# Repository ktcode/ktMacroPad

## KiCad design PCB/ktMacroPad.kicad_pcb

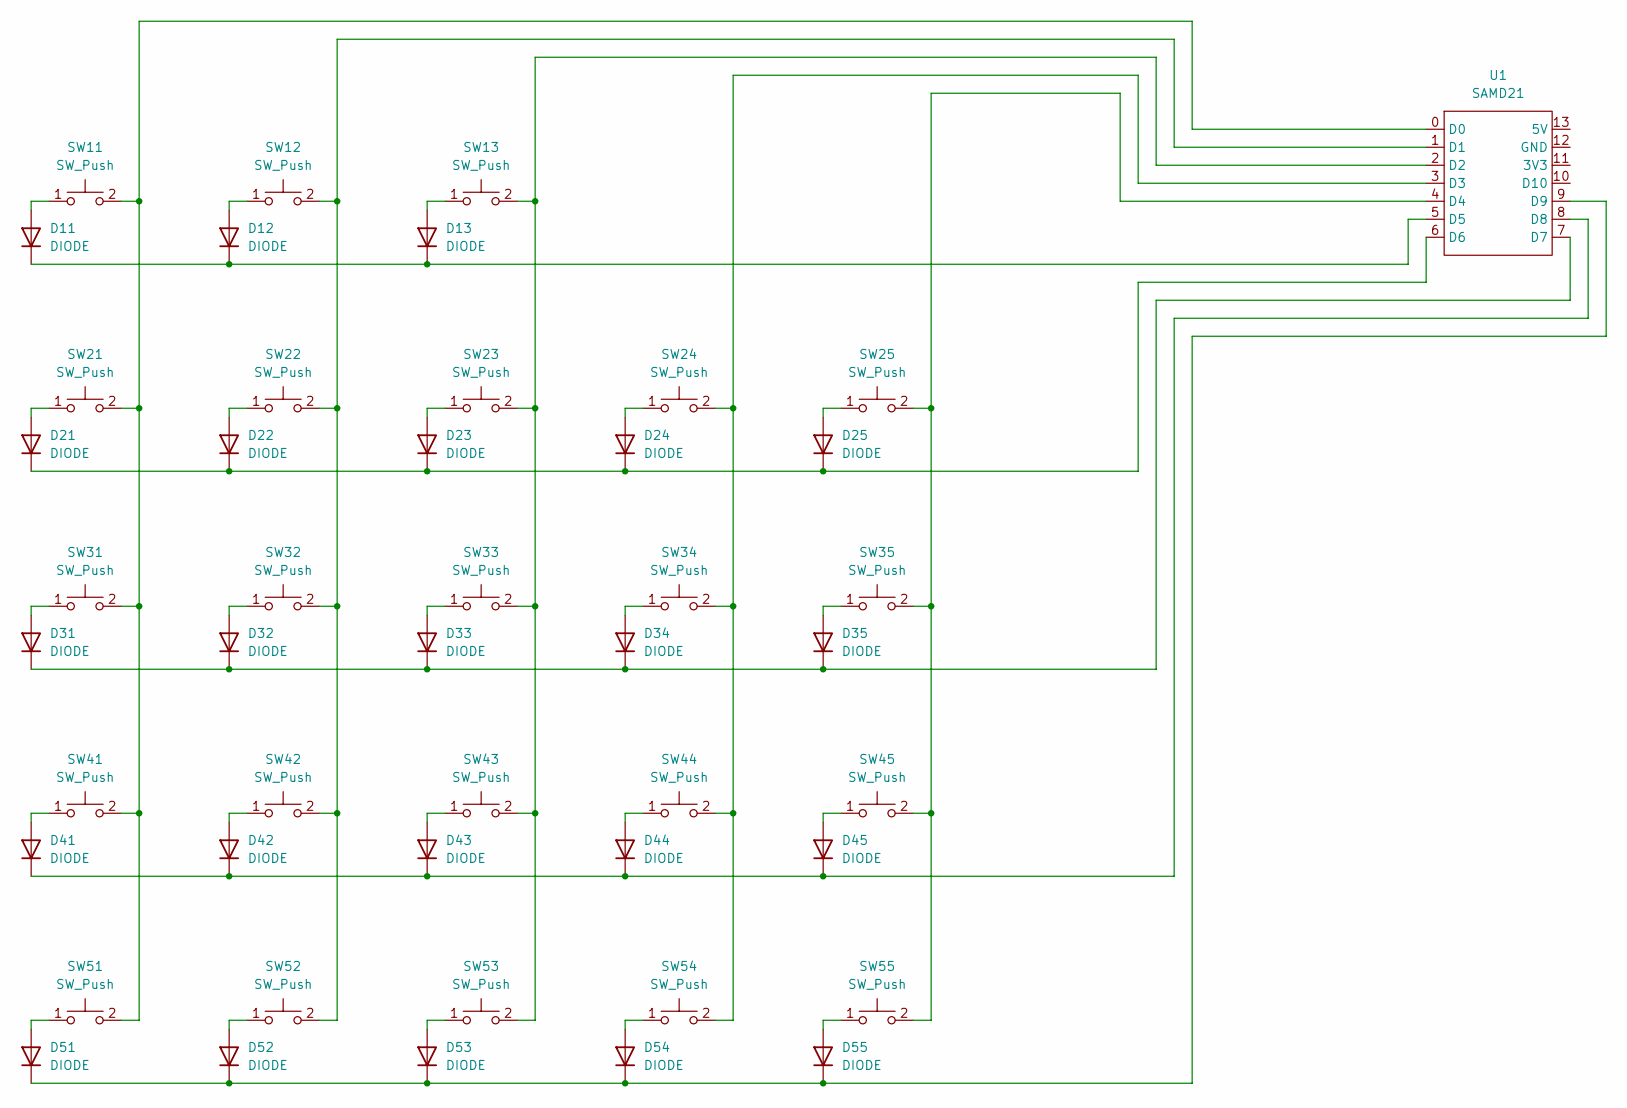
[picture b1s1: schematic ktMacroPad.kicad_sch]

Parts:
D11, D12, D13, D21, D22, D23, D24, D25, D31, D32, D33, D34, D35, D41, D42, D43, D44, D45, D51, D52, D53, D54, D55: DIODE; DI
SW11, SW12, SW13, SW21, SW22, SW23, SW24, SW25, SW31, SW32, SW33, SW34, SW35, SW41, SW42, SW43, SW44, SW45, SW51, SW52, SW53, SW54, SW55: SW_Push; MX_Choc_Socket
U1: SAMD21; Seeed xiao

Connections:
unnamed: D11.1 (A), SW11.1
unnamed: D11.2 (K), D12.2 (K), D13.2 (K), U1.5 (D5)
unnamed: D12.1 (A), SW12.1
unnamed: D13.1 (A), SW13.1
unnamed: D21.1 (A), SW21.1
unnamed: D21.2 (K), D22.2 (K), D23.2 (K), D24.2 (K), D25.2 (K), U1.6 (D6)
unnamed: D22.1 (A), SW22.1
unnamed: D23.1 (A), SW23.1
unnamed: D24.1 (A), SW24.1
unnamed: D25.1 (A), SW25.1
unnamed: D31.1 (A), SW31.1
unnamed: D31.2 (K), D32.2 (K), D33.2 (K), D34.2 (K), D35.2 (K), U1.7 (D7)
unnamed: D32.1 (A), SW32.1
unnamed: D33.1 (A), SW33.1
unnamed: D34.1 (A), SW34.1
unnamed: D35.1 (A), SW35.1
unnamed: D41.1 (A), SW41.1
unnamed: D41.2 (K), D42.2 (K), D43.2 (K), D44.2 (K), D45.2 (K), U1.8 (D8)
unnamed: D42.1 (A), SW42.1
unnamed: D43.1 (A), SW43.1
unnamed: D44.1 (A), SW44.1
unnamed: D45.1 (A), SW45.1
unnamed: D51.1 (A), SW51.1
unnamed: D51.2 (K), D52.2 (K), D53.2 (K), D54.2 (K), D55.2 (K), U1.9 (D9)
unnamed: D52.1 (A), SW52.1
unnamed: D53.1 (A), SW53.1
unnamed: D54.1 (A), SW54.1
unnamed: D55.1 (A), SW55.1
unnamed: SW11.2, SW21.2, SW31.2, SW41.2, SW51.2, U1.0 (D0)
unnamed: SW12.2, SW22.2, SW32.2, SW42.2, SW52.2, U1.1 (D1)
unnamed: SW13.2, SW23.2, SW33.2, SW43.2, SW53.2, U1.2 (D2)
unnamed: SW24.2, SW34.2, SW44.2, SW54.2, U1.3 (D3)
unnamed: SW25.2, SW35.2, SW45.2, SW55.2, U1.4 (D4)

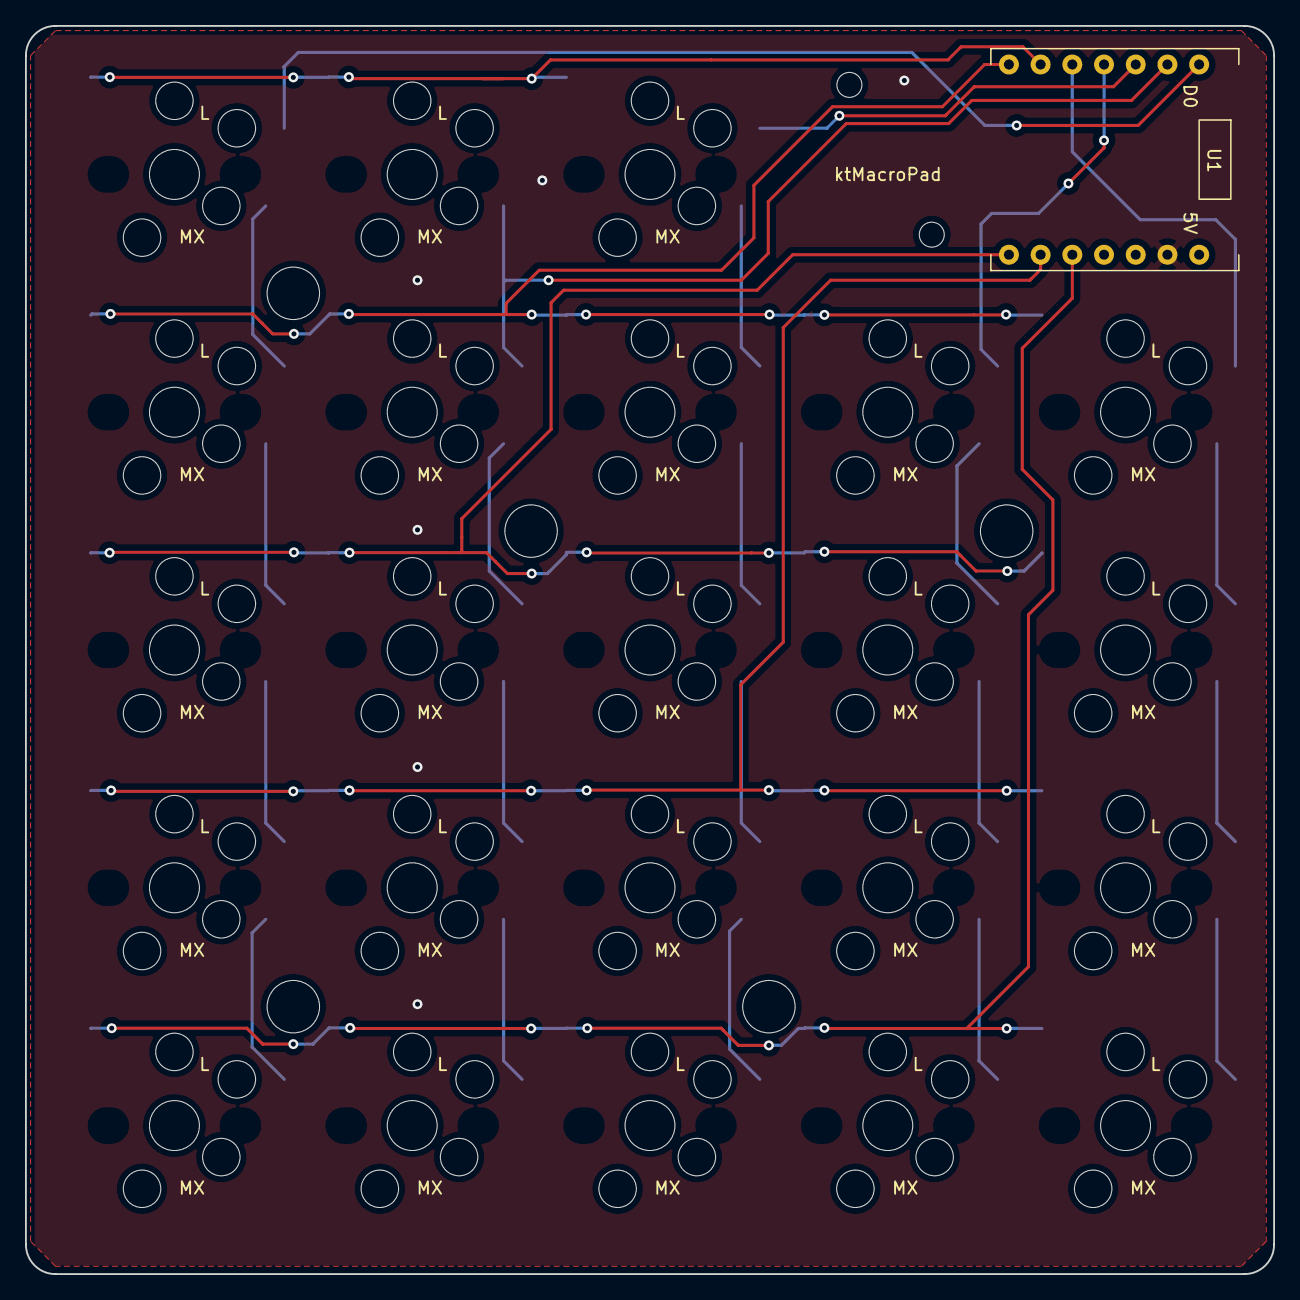
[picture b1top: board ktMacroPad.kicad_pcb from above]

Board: 2 copper layers, 100.0 x 100.0 mm, 47 parts (0 on the bottom side), 33 nets.

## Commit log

2025-06-25 latest
2025-06-25 Arduino
